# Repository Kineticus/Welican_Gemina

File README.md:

# Welican Gemina

A custom ESP32 module that controls WS2811 lights, a 1.3" OLED I2C, a MSGEQ7 Microphone board, and 2 encoders.

```
Your README file is normally the first entry point to your code. It should tell people why they should use your module, how they can install it, and how they can use it. Standardizing how you write your README makes creating and maintaining your READMEs easier. Great documentation takes work!
```

This repository contains:

1. [Board Design](BOARD_DESIGN.md) to show the custom ESP32 boarddesigned for this project.

## TODOs

- WIFI Manager
- ~~Saving Favorites~~
  - ~~Favorites Menu~~
- ~~Settings~~
  - ~~Set Led Count~~
  - ~~Show IP~~
  - Timeout (short, medium, long, extra long, never)
    - Show Weather/Clock
    - Turn off
  - ~~Clock Types~~
  - ~~Random Mode Speed (short, medium, long, extra long, never)~~
  - ~~Color Order (RGB, GRB, etc)~~
  - ~~Factory Reset (reset EPROM values to default, favorites, highscores)~~
- ~~Random Mode at beginning of categories~~
- ~~Fade between patterns (to prevent quick spins on pattern knob)~~
- Audio Input morphs Music Visualizer category lights
- More visualizers (VZ)
  - Random VZ for each category (at the beginning of category)
  - Differnt types of random (at the end of category)
- ~~Weather status~~
  - ~~By Zipcode~~
  - VZ based on weather
- ~~Get Time~~
  - ~~Show time in top menu~~

## Table of Contents

- [Background](#background)
- [Install](#install)
  - [Install Arduino Libraries](#install-arduino-libraries)
  - [VS Code & C++](#vs-code-&-c++)
- [Related Documents](#related-documents)
- [Maintainers](#maintainers)
- [Contributing](#contributing)
- [Helpful Links](#helpful-links)
- [FastLed Examples](#fastled-examples)
- [License](#license)

## Background
```
  // TODO add stuff
```
## Install

This project requires the [Arduino IDE](https://www.arduino.cc/en/Main/Software).

1. Install [Arduino IDE](https://www.arduino.cc/en/Main/Software).
2. In the Ardunio IDE, go to `File > Preferences` (CTRL + Comma).

3. Enter `https://dl.espressif.com/dl/package_esp32_index.json` into the “Additional Board Manager URLs” field as shown in the figure below. Then, click the “OK” button.

  - Note: if you already have the ESP8266 boards URL, you can separate the URLs with a comma as follows:
  `https://dl.espressif.com/dl/package_esp32_index.json, http://arduino.esp8266.com/stable/package_esp8266com_index.json`

4. Open the Boards Manager. Go to `Tools > Board > Boards Manager`

5. Search for ESP32 and press install button for the “ESP32 by Espressif Systems“

    - That’s it! Make sure to change the Board under the Tools menu to “ESP32 Dev Module”

### Install Arduino Libraries

6. Libraries `Tools > Manage Libraries` (Location is User Directory\Documents\Arduino\libraries)
  - [ESP32Encoder](https://github.com/madhephaestus/ESP32Encoder)
  - [FastLED](https://github.com/FastLED/FastLED/wiki)
    - [FastLED Samguyer Fork](https://github.com/samguyer/FastLED) *Optional
  - [arduinoFFT](https://github.com/kosme/arduinoFFT)
  - [U8g2](https://github.com/olikraus/u8g2/wiki/u8g2reference)
  - [ESPAsyncWebServer](https://github.com/me-no-dev/ESPAsyncWebServer) *Must be installed manually
  - [ASyncTCP](https://github.com/me-no-dev/AsyncTCP) *Must be installed manually
  - [ESP32 File System Tool](https://github.com/me-no-dev/arduino-esp32fs-plugin) *Must be installed manually by copying to Tools folder!! Read instructions carefully.
  
### Create Wifi Credentials file

7. Create a file called `Secrets.h` in the main folder.
That file should include the following:
```
#define WIFI_SSID "your-wifi-ssid-goes-here"
#define WIFI_PASSWORD "your-wifi-password-goes-here"
#define OPEN_WEATHER_API_KEY "your-open-weather-api-key"
```

You will need to replace the strings with your WIFI SSID and PASSWORD

### VS Code & C++
  - [.vscode/c_app_properties.json](https://code.visualstudio.com/docs/cpp/customize-default-settings-cpp)
  - [Arduino Extension](https://marketplace.visualstudio.com/items?itemName=vsciot-vscode.vscode-arduino)
  - [C++ Extension](https://marketplace.visualstudio.com/items?itemName=ms-vscode.cpptools)
  - [GitLens Extension](https://marketplace.visualstudio.com/items?itemName=eamodio.gitlens)

## Related Documents

- [Welican Project Doc](https://docs.google.com/document/d/e/2PACX-1vS1qt4seWkiZLkJHX4LD_V3VYEt1su2fU610a7UOJ1a_LkRgppqzjMMRaHVzRj_jQmDRsJIRdGVeDGK/pub) - The brain-dump file created by @Kinectus
- [BOM](https://docs.google.com/spreadsheets/d/1Lj1XwBXrHm5YGtD2jA4sHXP_yh42TAKp-GVNhS_lHCg/edit?usp=sharing) - Price / Cost spreadsheet created by @Kinectus

## Maintainers

  - [@Kinectus](https://github.com/Kineticus/)

  - [@MaylorTaylor](https://github.com/MaylorTaylor/)

## Contributing

Feel free to dive in! [Open an issue](https://github.com/Kineticus/Welican_Gemina/issues/new) or submit PRs.

Standard Readme follows the [Contributor Covenant](http://contributor-covenant.org/version/1/3/0/) Code of Conduct.

## Helpful Links

  - [C++ Classes](https://www.stroustrup.com/C++11FAQ.html#member-init)
  - [Custom XBM Image Convert](https://www.online-utility.org/image/convert/to/XBM)
  - [Arduino C++ & VSCode](https://learn.sparkfun.com/tutorials/efficient-arduino-programming-with-arduino-cli-and-visual-studio-code/all)
  - [Arduino Intellisense VSCode](https://cuneyt.aliustaoglu.biz/en/enabling-arduino-intellisense-with-visual-studio-code/)
  - [Experimental FastLED RGBSet](https://github.com/FastLED/FastLED/wiki/RGBSet-Reference)
  - [Refactoring out DELAY](https://forum.arduino.cc/index.php?topic=537644.0)
  - [UG82 Screen Library](https://github.com/olikraus/u8g2)
  - [Strings for CPP](https://cpp4arduino.com/2018/11/21/eight-tips-to-use-the-string-class-efficiently.html)

## FastLED Examples

  - [Demos](https://github.com/atuline/FastLED-Demos)
  - [Demos 2](https://github.com/marmilicious/FastLED_examples)
  - [Demos 3](https://www.tweaking4all.com/hardware/arduino/adruino-led-strip-effects/)
  - [Flagpole](https://github.com/chemdoc77/CD77_FastLED_Projects/tree/master/CD77_Flagpole_Project)
  - [Chase Demo](https://github.com/chemdoc77/CD77_FastLED/tree/master/CD77_Chase_Demo)

## License

[MIT License](/LICENSE.md) © Welican LLC

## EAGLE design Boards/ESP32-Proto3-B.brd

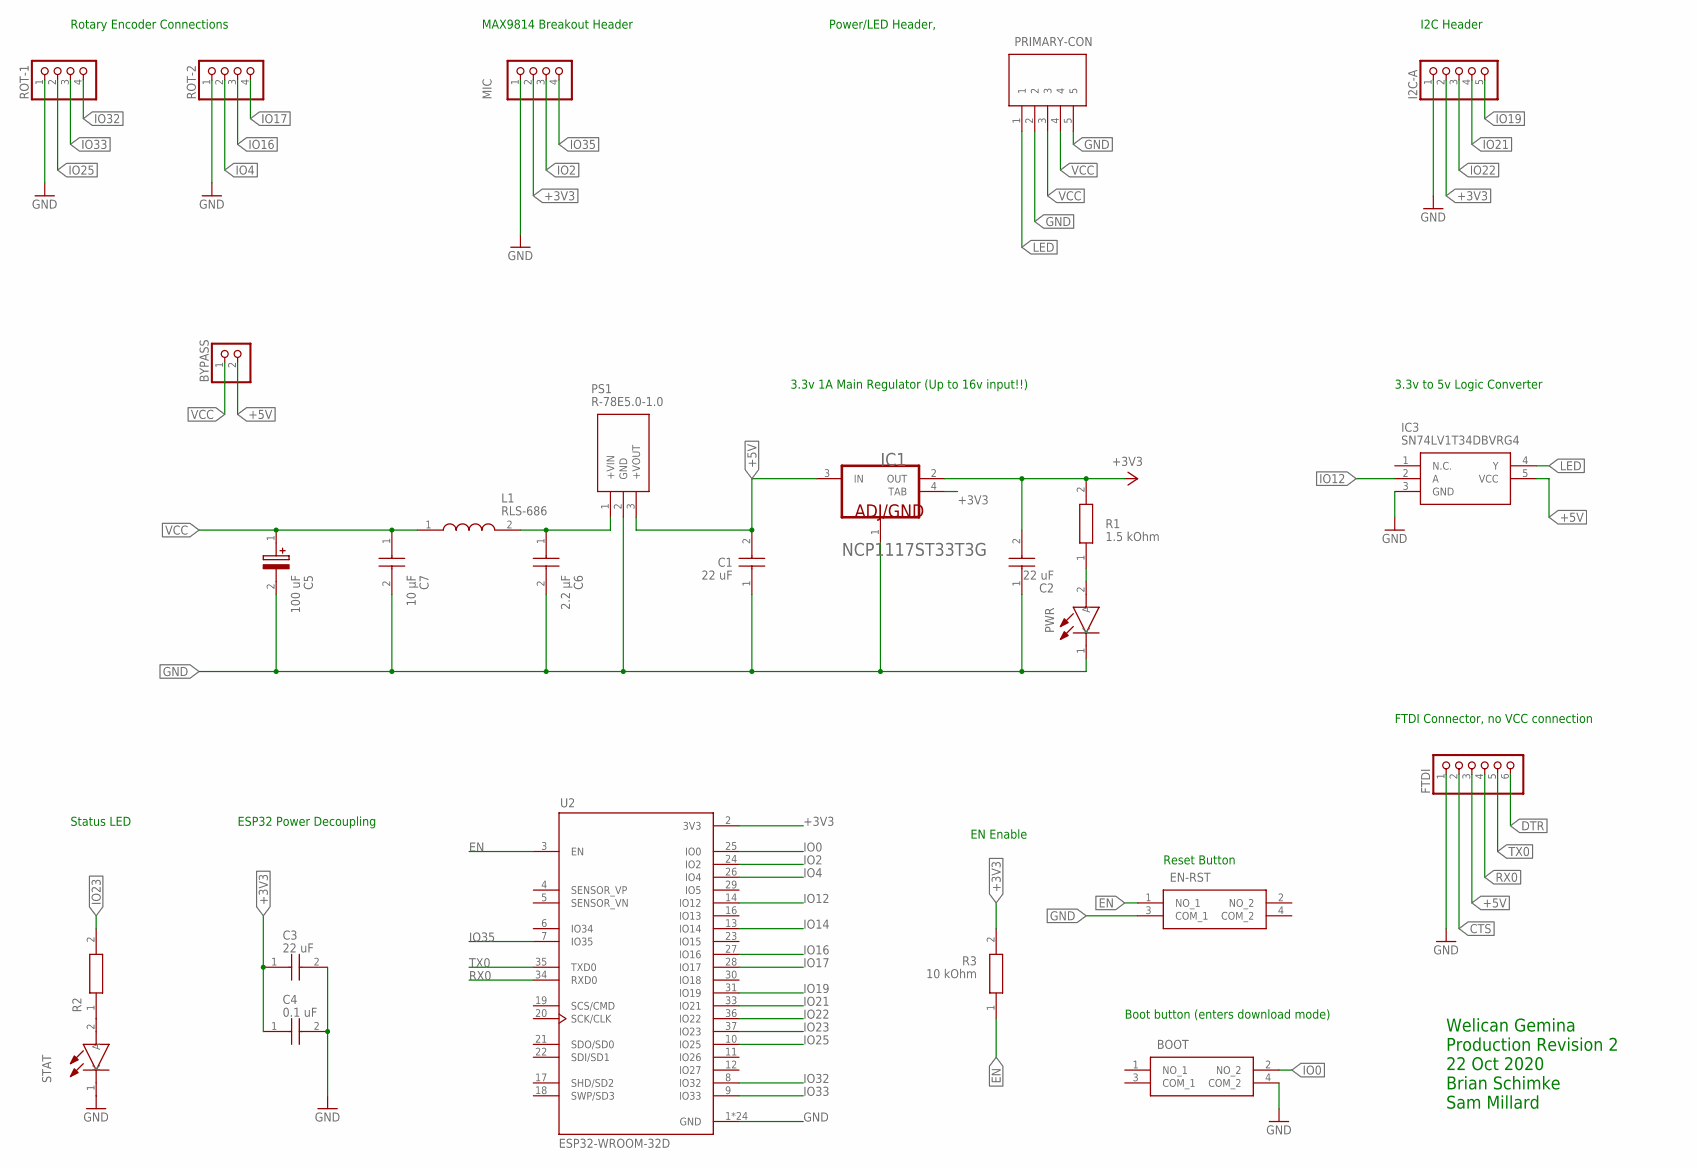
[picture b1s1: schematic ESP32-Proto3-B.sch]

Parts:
BOOT: PTS647SK70SMTR2LFS
BYPASS: PINHD-1X2; 1X02
C1, C2, C3: 22 uF; CAPC3216X180N
C4: 0.1 uF; CAPC3216X180N
C5: 100 uF; CAPAE660X770N
C6: 2.2 μF; CAPC3216X180N
C7: 10 μF; CAPC3216X180N
EN-RST: PTS647SK70SMTR2LFS
FTDI: PINHD-1X6; 1X06
I2C-A: PINHD-1X5; 1X05
IC1: ON_SEMICONDUCTOR_NCP1117ST33T3GON_SEMICONDUCTOR_N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; ON_SEMICONDUCTOR_NCP1117ST33T3G_0
IC3: SN74LV1T34DBVRG4; SOT95P280X145-5N
L1: RLS-686; RLS686
MIC: PINHD-1X4; 1X04
PRIMARY-CON: 1984646
PS1: R-78E5.0-1.0; R78E5010
PWR: 150120AS75000; LEDSC320X160X78-2N
R1: 1.5 kOhm; RESC3216X60N
R2: CRCW12061K00FKEB; RESC3216X60N
R3: 10 kOhm; RESC3216X60N
ROT-1, ROT-2: PINHD-1X4; 1X04
STAT: 150120AS75000; LEDSC320X160X78-2N
U2: ESP32-WROOM-32D; MODULE_ESP32-WROOM-32D

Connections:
+3V3: C2.2, C3.1, C4.1, I2C-A.2, IC1.2 (OUT), IC1.4 (TAB), MIC.2, R1.2, R3.2, U2.2 (3V3)
+5V: BYPASS.2, C1.2, FTDI.3, IC1.3 (IN), IC3.5 (VCC), PS1.3 (+VOUT)
CTS: FTDI.2
DTR: FTDI.6
EN: EN-RST.1 (NO_1), R3.1, U2.3 (EN)
GND: BOOT.4 (COM_2), C1.1, C2.1, C3.2, C4.2, C5.2 (-), C6.2, C7.2, EN-RST.3 (COM_1), FTDI.1, I2C-A.1, IC1.1 (ADJ/GND), IC3.3 (GND), MIC.1, PRIMARY-CON.2, PRIMARY-CON.5, PS1.2 (GND), PWR.1 (K), ROT-1.1, ROT-2.1, STAT.1 (K), U2.1 (GND), U2.15 (GND), U2.38 (GND), U2.39_1 (GND), U2.39_2 (GND), U2.39_3 (GND), U2.39_4 (GND), U2.39_5 (GND), U2.39_6 (GND), U2.39_7 (GND), U2.39_8 (GND), U2.39_9 (GND), U2.39_10 (GND), U2.39_11 (GND), U2.39_12 (GND), U2.39_13 (GND), U2.39_14 (GND), U2.39_15 (GND), U2.39_16 (GND), U2.39_17 (GND), U2.39_18 (GND), U2.39_19 (GND), U2.39_20 (GND), U2.39_21 (GND)
IO0: BOOT.2 (NO_2), U2.25 (IO0)
IO2: MIC.3, U2.24 (IO2)
IO4: ROT-2.2, U2.26 (IO4)
IO12: IC3.2 (A), U2.14 (IO12)
IO14: U2.13 (IO14)
IO16: ROT-2.3, U2.27 (IO16)
IO17: ROT-2.4, U2.28 (IO17)
IO19: I2C-A.5, U2.31 (IO19)
IO21: I2C-A.4, U2.33 (IO21)
IO22: I2C-A.3, U2.36 (IO22)
IO23: R2.2, U2.37 (IO23)
IO25: ROT-1.2, U2.10 (IO25)
IO32: ROT-1.4, U2.8 (IO32)
IO33: ROT-1.3, U2.9 (IO33)
IO35: MIC.4, U2.7 (IO35)
LED: IC3.4 (Y), PRIMARY-CON.1
unnamed: PWR.2 (A), R1.1
unnamed: R2.1, STAT.2 (A)
RX0: FTDI.4, U2.34 (RXD0)
TX0: FTDI.5, U2.35 (TXD0)
VCC: BYPASS.1, C5.1 (+), C7.1, L1.1, PRIMARY-CON.3, PRIMARY-CON.4
VIN: C6.1, L1.2, PS1.1 (+VIN)

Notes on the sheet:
ESP32 Power Decoupling
EN Enable
3.3v to 5v Logic Converter
Reset Button
Boot button (enters download mode)
3.3v 1A Main Regulator (Up to 16v input!!)
Status LED
FTDI Connector, no VCC connection
Rotary Encoder Connections
I2C Header
Power/LED Header,
MAX9814 Breakout Header
Welican Gemina Production Revision 2 22 Oct 2020 Brian Schimke Sam Millard

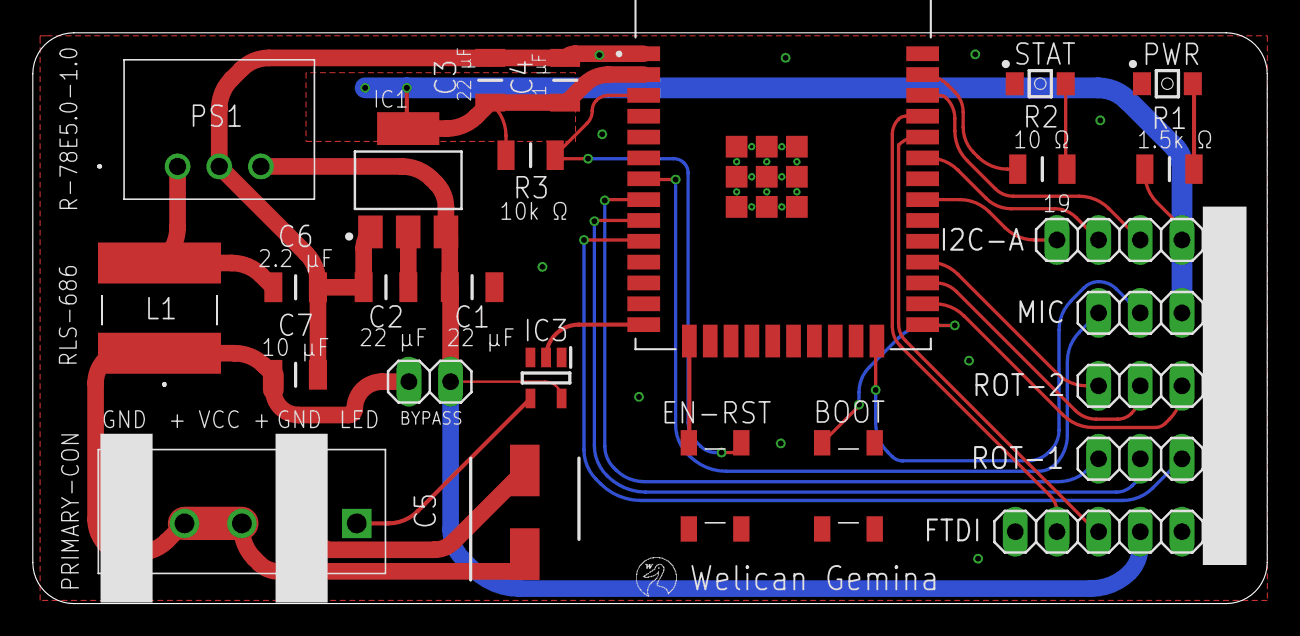
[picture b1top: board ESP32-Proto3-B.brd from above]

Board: 2 copper layers, 75.2 x 34.8 mm, 26 parts (0 on the bottom side), 25 nets.

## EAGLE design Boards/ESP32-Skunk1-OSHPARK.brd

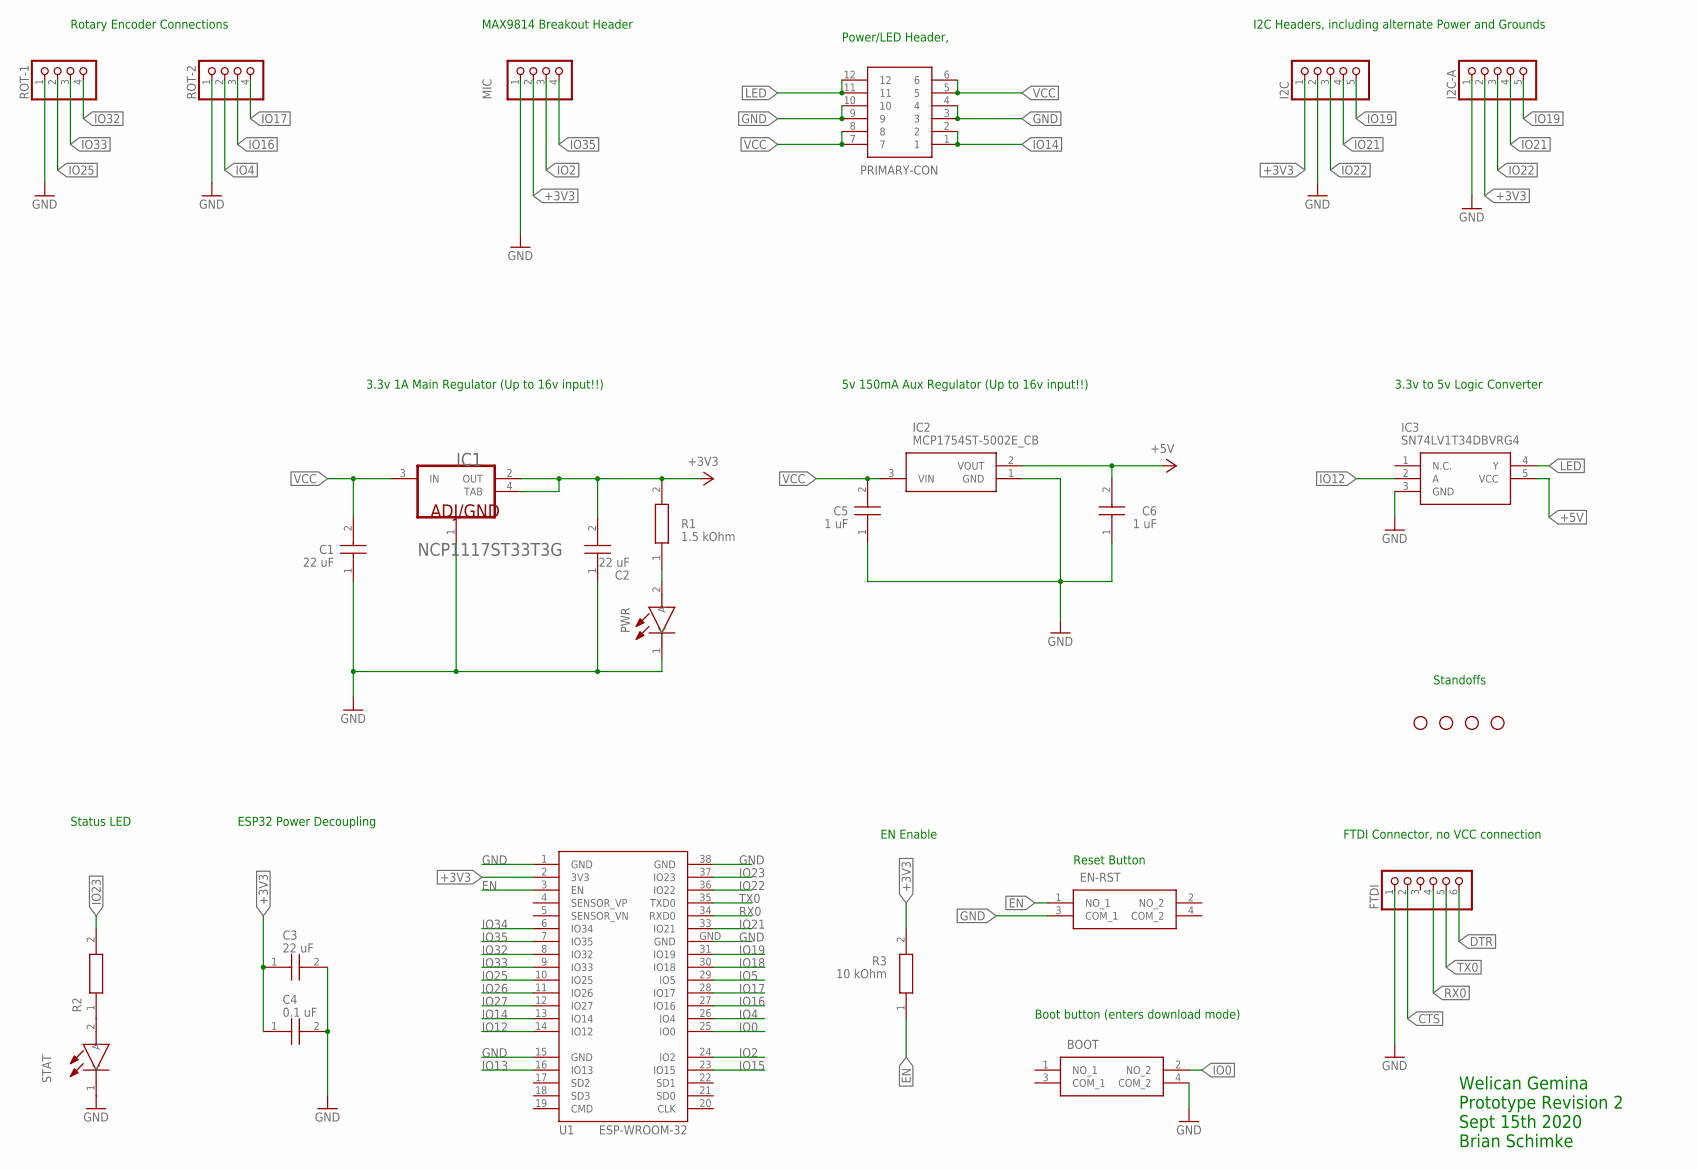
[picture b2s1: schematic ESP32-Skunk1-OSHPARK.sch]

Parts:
BOOT: PTS647SK70SMTR2LFS
C1, C2, C3: 22 uF; CAPC3216X180N
C4: 0.1 uF; CAPC3216X180N
C5, C6: 1 uF; CAPC3216X180N
EN-RST: PTS647SK70SMTR2LFS
FTDI: PINHD-1X6; 1X06
H1, H2, H3, H4: STAND-OFF
I2C, I2C-A: PINHD-1X5; 1X05
IC1: ON_SEMICONDUCTOR_NCP1117ST33T3GON_SEMICONDUCTOR_N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; ON_SEMICONDUCTOR_NCP1117ST33T3G_0
IC2: MCP1754ST-5002E_CB; SOT95P255X145-3N
IC3: SN74LV1T34DBVRG4; SOT95P280X145-5N
MIC: PINHD-1X4; 1X04
PRIMARY-CON: 1-2834015-6; SHDR12W90P508X254_2X6_1824X128
PWR: 150120AS75000; LEDSC320X160X78-2N
R1: 1.5 kOhm; RESC3216X60N
R2: CRCW12061K00FKEB; RESC3216X60N
R3: 10 kOhm; RESC3216X60N
ROT-1, ROT-2: PINHD-1X4; 1X04
STAT: 150120AS75000; LEDSC320X160X78-2N
U1: ESP-WROOM-32

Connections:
+3V3: C2.2, C3.1, C4.1, I2C.1, I2C-A.2, IC1.2 (OUT), IC1.4 (TAB), MIC.2, R1.2, R3.2, U1.2 (3V3)
+5V: C6.2, IC2.2 (VOUT), IC3.5 (VCC)
CTS: FTDI.2
DTR: FTDI.6
EN: EN-RST.1 (NO_1), R3.1, U1.3 (EN)
GND: BOOT.4 (COM_2), C1.1, C2.1, C3.2, C4.2, C5.1, C6.1, EN-RST.3 (COM_1), FTDI.1, I2C.2, I2C-A.1, IC1.1 (ADJ/GND), IC2.1 (GND), IC3.3 (GND), MIC.1, PRIMARY-CON.3, PRIMARY-CON.4, PRIMARY-CON.9, PRIMARY-CON.10, PWR.1 (K), ROT-1.1, ROT-2.1, STAT.1 (K), U1.1 (GND), U1.15 (GND), U1.38 (GND), U1.GND
IO0: BOOT.2 (NO_2), U1.25 (IO0)
IO2: MIC.3, U1.24 (IO2)
IO4: ROT-2.2, U1.26 (IO4)
IO5: U1.29 (IO5)
IO12: IC3.2 (A), U1.14 (IO12)
IO13: U1.16 (IO13)
IO14: PRIMARY-CON.1, PRIMARY-CON.2, U1.13 (IO14)
IO15: U1.23 (IO15)
IO16: ROT-2.3, U1.27 (IO16)
IO17: ROT-2.4, U1.28 (IO17)
IO18: U1.30 (IO18)
IO19: I2C.5, I2C-A.5, U1.31 (IO19)
IO21: I2C.4, I2C-A.4, U1.33 (IO21)
IO22: I2C.3, I2C-A.3, U1.36 (IO22)
IO23: R2.2, U1.37 (IO23)
IO25: ROT-1.2, U1.10 (IO25)
IO26: U1.11 (IO26)
IO27: U1.12 (IO27)
IO32: ROT-1.4, U1.8 (IO32)
IO33: ROT-1.3, U1.9 (IO33)
IO34: U1.6 (IO34)
IO35: MIC.4, U1.7 (IO35)
LED: IC3.4 (Y), PRIMARY-CON.11, PRIMARY-CON.12
unnamed: PWR.2 (A), R1.1
unnamed: R2.1, STAT.2 (A)
RX0: FTDI.4, U1.34 (RXD0)
TX0: FTDI.5, U1.35 (TXD0)
VCC: C1.2, C5.2, IC1.3 (IN), IC2.3 (VIN), PRIMARY-CON.5, PRIMARY-CON.6, PRIMARY-CON.7, PRIMARY-CON.8

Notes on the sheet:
ESP32 Power Decoupling
EN Enable
3.3v to 5v Logic Converter
Reset Button
Boot button (enters download mode)
3.3v 1A Main Regulator (Up to 16v input!!)
Status LED
5v 150mA Aux Regulator (Up to 16v input!!)
FTDI Connector, no VCC connection
Rotary Encoder Connections
I2C Headers, including alternate Power and Grounds
Power/LED Header,
MAX9814 Breakout Header
Standoffs
Welican Gemina Prototype Revision 2 Sept 15th 2020 Brian Schimke

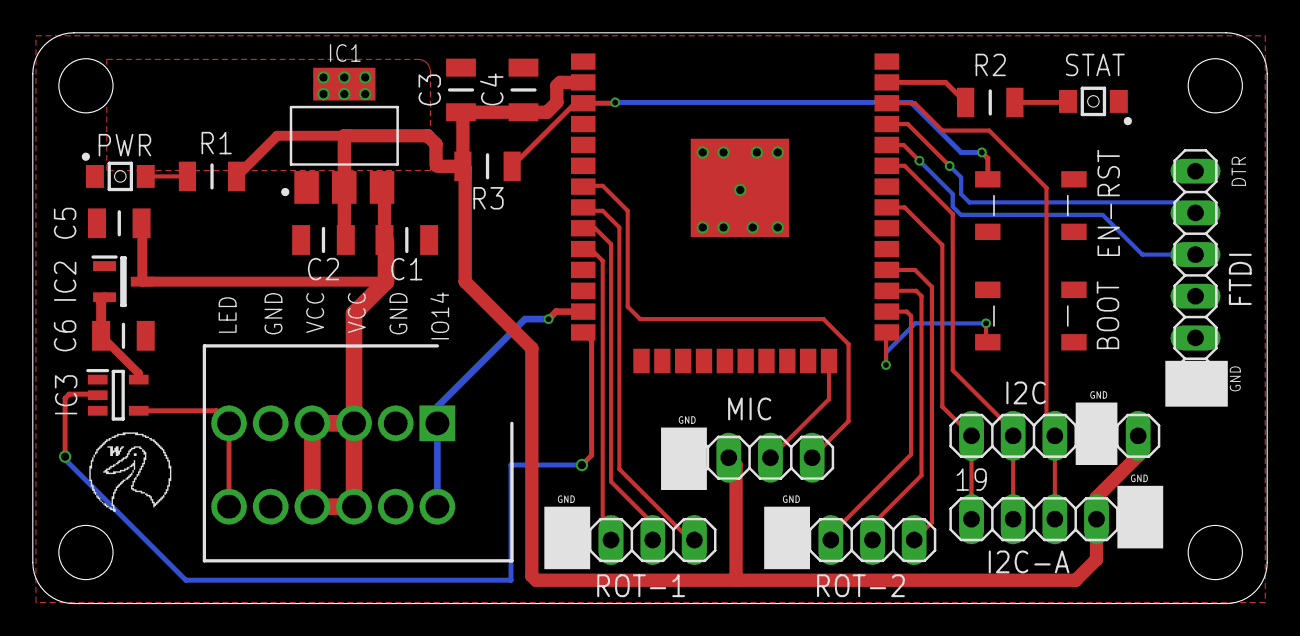
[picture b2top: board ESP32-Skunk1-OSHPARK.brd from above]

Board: 2 copper layers, 75.2 x 34.8 mm, 28 parts (0 on the bottom side), 25 nets.

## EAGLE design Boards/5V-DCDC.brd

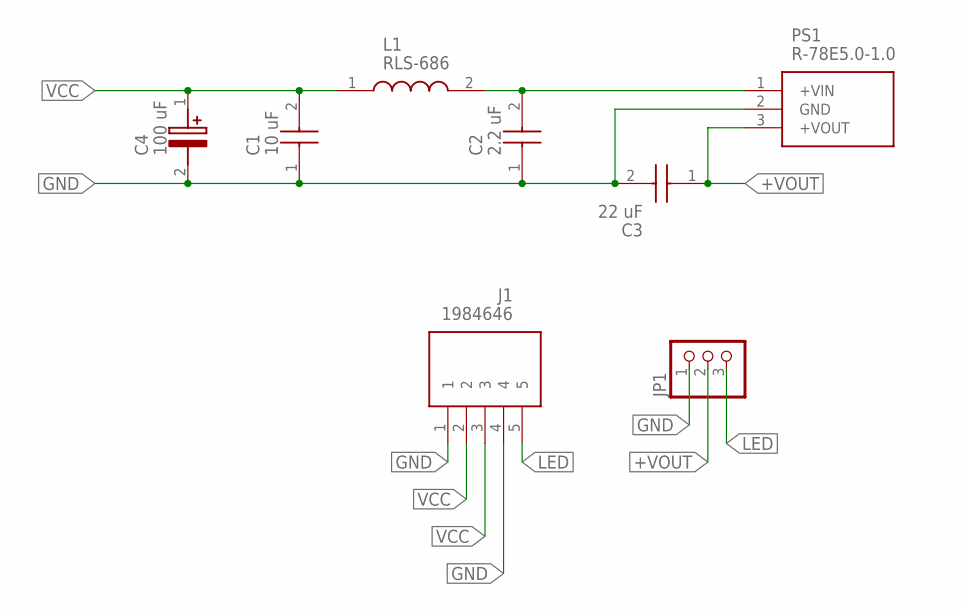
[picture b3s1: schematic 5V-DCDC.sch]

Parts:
C1: 10 uF; CAPC3216X180N
C2: 2.2 uF; CAPC3216X180N
C3: 22 uF; CAPC3216X180N
C4: 100 uF; CAPAE660X770N
J1: 1984646
JP1: PINHD-1X3; 1X03
L1: RLS-686; RLS686
PS1: R-78E5.0-1.0; R78E5010

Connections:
+VIN: C2.2, L1.2, PS1.1 (+VIN)
+VOUT: C3.1, JP1.2, PS1.3 (+VOUT)
GND: C1.1, C2.1, C3.2, C4.2 (-), J1.1, J1.4, JP1.1, PS1.2 (GND)
LED: J1.5, JP1.3
VCC: C1.2, C4.1 (+), J1.2, J1.3, L1.1

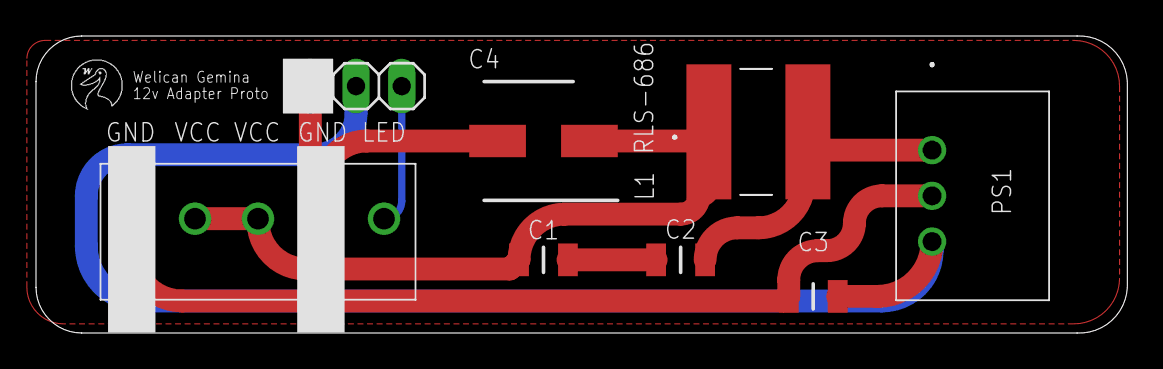
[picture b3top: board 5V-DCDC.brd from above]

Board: 2 copper layers, 60.6 x 16.5 mm, 8 parts (0 on the bottom side), 5 nets.

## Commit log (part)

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2020-09-28 Even better Smooth Operator, 100th commit!
2020-09-28 Smooth Operator refinements
2020-09-28 Time/NTP Sync
2020-09-28 Small fixes for network time & favorites
2020-09-29 Timezone and DST fixes
2020-09-29 Timezone fixes
2020-09-30 added HTTP GET requests for weather, commented out cause cuoldn't get working
2020-09-30 removed broken httpclient code
2020-09-30 fixed compile err
2020-09-30 Getting weather data via JSON
2020-09-30 added weather description on screen
2020-09-30 cleaned up open weather code
2020-09-30 fixed serial print for weather
2020-09-30 added weathersettings struct
2020-09-30 added time struct
2020-09-30 removed old time struct
2020-09-30 removed unused variables
2020-09-30 fixed open weather object
2020-09-30 added more weather variables
2020-10-01 rearranged main file
2020-10-01 rearranged global variables and fallios game
2020-10-01 created Player struct
2020-10-01 added globals struct
2020-10-01 rearranged things
2020-10-01 rearranged some thigns
2020-10-01 Small patch and changes to debug logging
2020-10-01 added time converter function and unix converter
2020-10-01 added star struct
2020-10-01 added some new globals
2020-10-01 created brightness struct
2020-10-01 added dvdmodel struct
2020-10-01 added devEnvironment variables/struct
2020-10-01 added curreSpeed to globals
2020-10-01 added newTime to globals
2020-10-01 added MODE variables to globals
2020-10-01 added current menu to globals
2020-10-01 added tempPattern to globals
2020-10-01 added pixelNumber to globals
2020-10-01 created globalLED struct
2020-10-01 fixed errors and made more defines for LED count
2020-10-01 added fade direction to globa led
2020-10-01 added fadeamount to brightness
2020-10-01 added some vars to brightness
2020-10-01 added PatternSettings
2020-10-01 fix build errors
2020-10-02 Added a cool clock
2020-10-02 Alternate clock
2020-10-02 New clocks & idle time system
2020-10-02 cleaning up more variables, simplex noise
2020-10-02 added more to pattern settings
2020-10-02 added more to simplex noise
2020-10-02 cleaned up variables and structs
2020-10-02 Fix typos
2020-10-02 updated website with category and function name
2020-10-02 added more things to structs
2020-10-02 Old Standard Clock Font
2020-10-02 Modern Style clock
2020-10-03 moved pattern, favorites into PatternSettings
2020-10-03 moved more things into PatternSettings
2020-10-03 maybe finished all structs?
2020-10-03 fixed error
2020-10-03 Patches
2020-10-03 ZIP Code Editor/Fixes
2020-10-03 ZIP Code Menu with Store/Recall
2020-10-04 Bug fixes
2020-10-04 Better EEPROM access
2020-10-04 WiFi Scan Menu, first test
2020-10-05 WiFi Manager! 200th Commit Special
2020-10-05 Captive Portal for Soft AP
2020-10-05 Allow normal WiFi + Soft AP Simultaneously
2020-10-06 updated menu code/comments
2020-10-06 cleaning up code
2020-10-06 added some better menu variables and structure for menus
2020-10-06 made input number menug
2020-10-06 added better bounce function
2020-10-06 added better star bounce
2020-10-06 changed starmodel to BallModel
2020-10-06 updated some image names to all CAPS
2020-10-06 updated err
2020-10-06 renamed game files
2020-10-06 cleaning things up
2020-10-06 made websiteHelper
2020-10-06 working on website for better optimization/loading
2020-10-06 movnig things aroudn
2020-10-06 added auto refresh on page
2020-10-06 fixing some website stuff
2020-10-06 working on website
2020-10-06 got loading gif working for website
2020-10-06 small changes
2020-10-06 working on loading of page
2020-10-06 EEPROM Changes from .write to .put
2020-10-07 Randomizer
2020-10-07 moved variables to Pattern Settings
2020-10-07 added space
2020-10-08 added magic words question outlien
2020-10-08 got magic game basic working
2020-10-08 fixed spacing of game name
2020-10-08 Fixed game
2020-10-08 Random mode back to 0, improvements
2020-10-08 getting layout of magic game better
2020-10-08 added more questions and answers to magic
2020-10-08 made resetQA
2020-10-08 fixed some spacing on magic game
2020-10-08 added more QA
2020-10-08 trying to get magic visual working
2020-10-08 Favorites fix and random improvements
2020-10-09 Wifi Signal Meter, menu tweaks
2020-10-09 Fallios now gets more difficult
2020-10-10 Set/Store/Recall Number of LEDs
2020-10-11 Interfade Settings
2020-10-11 Better WiFi Scan icons
2020-10-12 Slight menu rearrangement
2020-10-12 updated function name to be inline with naming conventions
2020-10-12 updated function names
2020-10-13 Imrpvoed knobX.heldTime function
2020-10-15 Screen Timeout Menu
2020-10-15 Music test
2020-10-15 'nother music category
2020-10-16 Set display timeout and type
2020-10-16 Fixed some bugs with display types and saving
2020-10-16 added some more music patterns
2020-10-16 added a weather tile
2020-10-16 removed font
2020-10-16 graphs
2020-10-16 added a 4 band eq test
2020-10-16 changed number of bands
2020-10-16 weather json udpate
2020-10-16 updating weather screen
2020-10-16 updated spacing
2020-10-16 updated unix time func
2020-10-16 timerd delay
2020-10-18 Fixed Midnight showing as 0 for Clocks
2020-10-18 Added Random Time settings with save and recall
2020-10-18 added more weather displays
2020-10-18 fixed case statement
2020-10-20 Band Averages & Better Graphing
2020-10-20 long term averages
2020-10-20 Support for future 2.4" OLED
2020-10-20 better drawEq
2020-10-20 working on adding settings to website
2020-10-20 adding settings to website
2020-10-22 Favorites from Web
2020-10-22 added sldier to website
2020-10-23 updated webiste to be better on phone
2020-10-23 added debounce to website helper for brightness
2020-10-23 removed auto refresh from website
2020-10-23 updated mobile ui
2020-10-23 removed refresh on website
2020-10-23 removed footer on website for mobile only
2020-10-24 New miniature board layout
2020-10-24 Cage Brewing
2020-10-26 Better pattern adjust screen concept
2020-10-26 Refinements to Pattern Adjust Concept
2020-10-26 Cleaning up Update Encoder code
2020-10-27 Pattern adjust graphic changes
2020-10-27 Favorites now saves adjustment setting as well
2020-10-27 Updated save favorite code
2020-10-28 changed Favorites to star icon
2020-10-28 Board stencils w/ drill sizes
2020-10-31 Starting a new Palette Mode
2020-11-02 New palette tests
2020-11-02 New palette mode
2020-11-05 Stable 30 FPS
2020-11-07 added two face smirk images
2020-11-07 Bug hunting
2020-11-07 Testing images
2020-11-07 added some more palletts
2020-11-08 added more palettes
2020-11-12 New Stencil
2020-11-15 Block Breaker Update
2020-11-16 Better Block Breaker mechanics
2020-11-16 New board designs
2020-11-16 Better hit detection for Block Breaker
2020-11-18 More levels for Block Breaker
2020-11-18 Starting Snake type game
2020-11-20 Beter Snake Game
2020-11-20 Just needs apples
2020-11-20 Hungry for Apples?
2020-11-21 Smooth fades for web changes
2020-11-21 More accurate variables for webpage
2020-11-21 Testing new menu setup
2020-11-22 Pong Game
2020-11-22 Better pong mechanics
2020-11-22 Pong updates
2020-11-24 Pong improvements
2020-11-26 Happy Thanksgiving!
2020-11-29 Fixed favorite saving glitch
2020-11-30 Starting 2P Snake
2020-12-02 Better clock faces
2020-12-04 Fixed sunrise and sunset times
2020-12-05 More display ideas
2020-12-06 Better clock functions
2020-12-06 Fleshed out Lava Lamp function
2020-12-06 More clock function improvements
2020-12-06 Lava update
2020-12-06 More lava stuff
2020-12-07 working on getting current and daily open call APIs
2020-12-07 added getCurrentWeather & getDailyWeather functions for better OpenWeatherApi integration
2020-12-07 got all 7 days + current day parsing from daily weather api call
2020-12-07 added better logging for open weather and fixed some parsing
2020-12-07 small adjustments to clock spacing
2020-12-07 catching up
2020-12-09 Scrolling menu function
2020-12-09 added google firebase real time database integration for user create and update
2020-12-09 updated gitignore to ignore secrets file
2020-12-09 added new function to update user data and added fallios highscore
2020-12-10 New menu layout
2020-12-11 Working on new display menus
2020-12-12 Multiple displays with unique timers, LED status
2020-12-13 Bug fix
2020-12-13 Brightness Menu
2020-12-13 Timezone Selection!
2020-12-13 working on the create user logic
2020-12-13 LED Blink when adding new favorite
2020-12-13 cant get delay user creation workign'
2020-12-13 added timerDelay to user
2020-12-13 cleaned things up
2020-12-14 adding better logic to create user
2020-12-14 Manual time entry
2020-12-14 added createdDate
2020-12-14 added categories, renamed/arranged cats, and set up for future advancements
2020-12-14 cleaned up copy/paste garbage
2020-12-14 Manual time entry beta
2020-12-14 got category select working
2020-12-14 updated visualizers for new categories
2020-12-14 Manual time entry betea 2
2020-12-14 removed Legacy_Category, kept freezing system. Whooops? Dunno how it happened. But I did make it so we have 9 category slots available. So LET'S EXPAND!
2020-12-14 got all new categories working with some new visuals to tell them apart
2020-12-14 adding some flair to the top menu
2020-12-14 changed some fonts around
2020-12-14 fixed if user exists check
2020-12-14 made it so it will not constantly check for user existing
2020-12-14 Updated Favorites menus for new categories
2020-12-14 added arudino.h file to help with references
2020-12-14 Legacy back for troubleshooting
2020-12-14 Fixed glitch with Legacy category
2020-12-14 added highscore capture to updateUserScores()
2020-12-14 fixed logic for updating user data
2020-12-14 fixed build errors
2020-12-14 fixed build errors again
2020-12-14 fixed more build errors
2020-12-14 rearranging some logic for creating/updating user
2020-12-15 refactored some small things and changed globalUser.timezone to INT
2020-12-15 updated create user logic to only create all user data in one push if WIFI is connected
2020-12-15 added VUE js project for highscore website framework
2020-12-15 removed EEPROM read because it stopped user from being created
2020-12-15 got highscore website basically working
2020-12-15 OpenWeather check now uses HTTP instead of HTTPS
2020-12-16 added PNG files of weather animations
2020-12-16 moved weather animations to own folder
2020-12-16 added all the weather animations in Code
2020-12-16 added all the new weather animation images (.BMP) into the project
2020-12-17 fixed name of score for daddy worm
2020-12-17 removed save button on modal
2020-12-17 added back in boards folder
2020-12-17 added back Boards and data folder to correct place
2020-12-18 Improved weather display
2020-12-18 Cleaning up patterns and unused functions
2020-12-18 Better legacy cat
2020-12-18 updated highscores website look
2020-12-18 deployed new highscore site
2020-12-18 Beta 1.0
2020-12-19 added better table sorting to highscore site
2020-12-19 Bring back Weather mode to develop
2020-12-19 Fixed weather pattern
2020-12-19 Small menu glitch
2020-12-19 testing animations
2020-12-20 added new display with dynamic weather icons and title/description
2020-12-20 added more displays
2020-12-20 fixed build error
2020-12-20 updated weather screen to look better
2020-12-20 added more displays to show off weather animations
2020-12-20 updating some spacing on animations
2020-12-20 cleaning up icon things
2020-12-20 adding some animation tests and new weather screens
2020-12-20 Spelling error fix, small changes
2020-12-20 updated some positioning of large temp numbers
2020-12-20 creating sunset/rise display
2020-12-20 Changed font
2020-12-20 adding new icons
2020-12-20 added new icons to favorites section
2020-12-20 repositioned icon in faves area
2020-12-22 More EEPROM adjustments
2020-12-23 More responsive buttons/encoders
2020-12-23 removed eeprom user exists comitt
2020-12-24 New palette
2020-12-28 Disable dithering
2020-12-29 Fixed bug when creating new favorite
2020-12-29 Snake game shows score
2020-12-30 Fixed power menu glitch
2020-12-30 Hold both buttons to exit, small glitch fixed
2020-12-31 Small updates
2020-12-31 Cooler Fallio score status markers
2021-01-01 reworked some decor pattern
2021-01-01 Fallios now has speed adjustment

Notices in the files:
parts and their libraries:
esp32: Creative Commons Attribution-ShareAlike 4.0 International
SparkFun-Hardware: Licensing: Creative Commons ShareAlike 4.0 International - https://creativecommons.org/licenses/by-sa/4.0
